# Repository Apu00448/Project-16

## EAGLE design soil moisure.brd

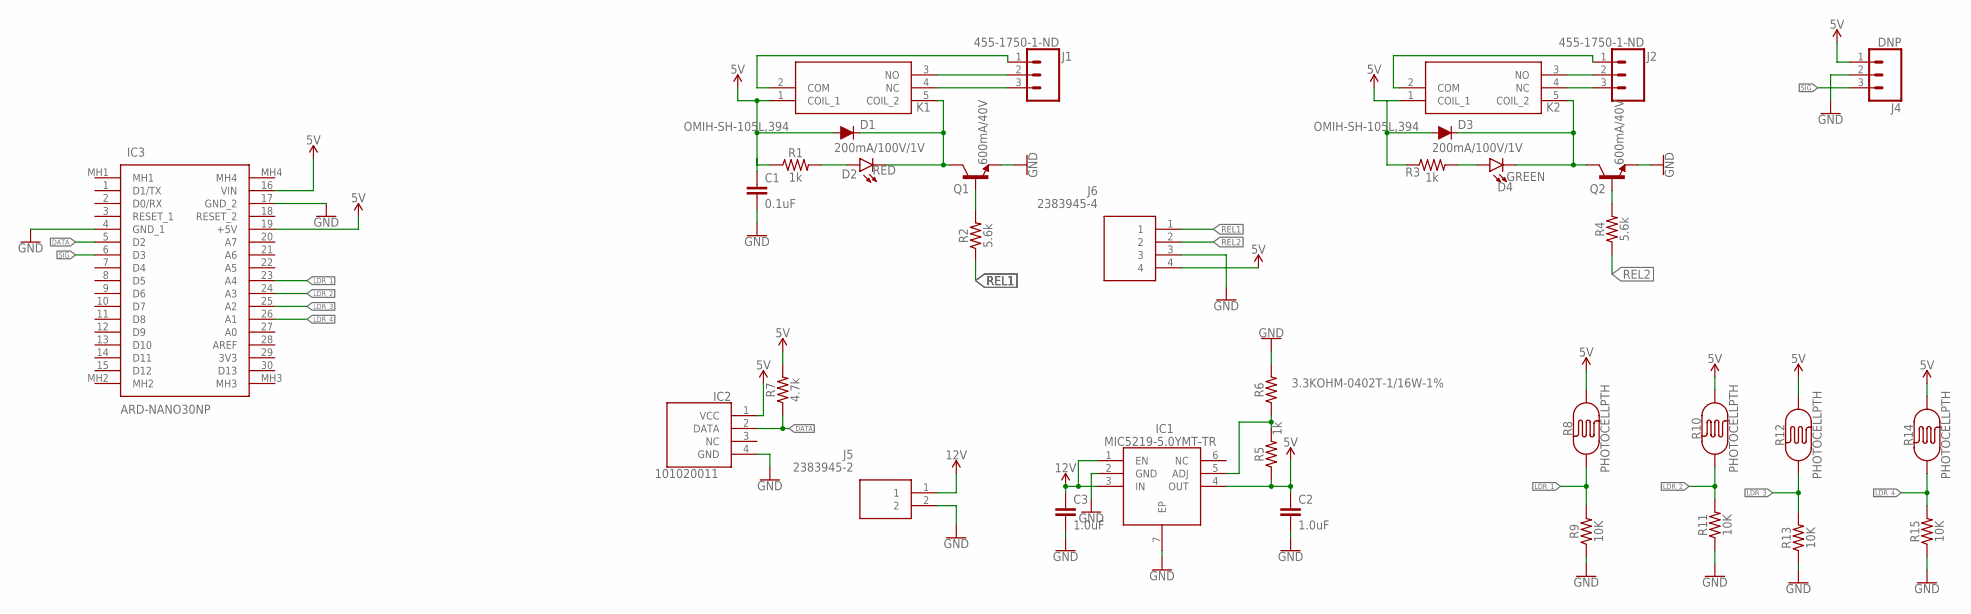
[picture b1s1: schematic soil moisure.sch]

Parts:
C1: 0.1uF; 0402-TIGHT
C2, C3: 1.0uF; 0402-TIGHT
D1, D3: 200mA/100V/1V; DIODE-1N4148
D2: RED; LED-0603
D4: GREEN; LED-0603
IC1: MIC5219-5.0YMT-TR; SON65P200X200X60-7N
IC2: 101020011; HDRV4W80P0X254_1X4_1200X500X15
IC3: ARD-NANO30NP; ARDNANO30NP
J1, J2: 455-1750-1-ND; 1X03
J4: DNP; MOLEX-1X3
J5: 2383945-2; 23839452
J6: 2383945-4; 23839454
K1, K2: OMIH-SH-105L,394; OMIHSH105L394
Q1, Q2: 600mA/40V; SOT23-3
R1, R3, R5: 1k; 0402-TIGHT
R2, R4: 5.6k; 0603
R6: 3.3KOHM-0402T-1/16W-1%; 0402-TIGHT
R7: 4.7k; 0402-TIGHT
R8, R10, R12, R14: PHOTOCELLPTH; PHOTOCELL
R9, R11, R13, R15: 10K; 0402-TIGHT

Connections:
5V: C2.1, D1.A, D3.A, IC1.4 (OUT), IC2.1 (VCC), IC3.16 (VIN), IC3.19 (+5V), J4.1, J6.4, K1.1 (COIL_1), K2.1 (COIL_1), R1.1, R3.1, R5.1, R7.2, R8.2, R10.2, R12.2, R14.2
12V: C3.1, IC1.1 (EN), IC1.3 (IN), J5.1
DATA: IC2.2 (DATA), IC3.5 (D2), R7.1
GND: C1.2, C2.2, C3.2, IC1.2 (GND), IC1.7 (EP), IC2.4 (GND), IC3.4 (GND_1), IC3.17 (GND_2), J4.2, J5.2, J6.3, Q1.2 (E), Q2.2 (E), R6.2, R9.1, R11.1, R13.1, R15.1
LDR_1: IC3.23 (A4), R8.1, R9.2
LDR_2: IC3.24 (A3), R10.1, R11.2
LDR_3: IC3.25 (A2), R12.1, R13.2
LDR_4: IC3.26 (A1), R14.1, R15.2
unnamed: J1.3, K1.4 (NC)
unnamed: J1.2, K1.3 (NO)
unnamed: J1.1, K1.2 (COM)
unnamed: D1.C, D2.C, K1.5 (COIL_2), Q1.3 (C)
unnamed: D2.A, R1.2
unnamed: J2.3, K2.4 (NC)
unnamed: Q1.1 (B), R2.2
unnamed: J2.2, K2.3 (NO)
unnamed: J2.1, K2.2 (COM)
unnamed: D3.C, D4.C, K2.5 (COIL_2), Q2.3 (C)
unnamed: D4.A, R3.2
unnamed: Q2.1 (B), R4.2
unnamed: IC1.5 (ADJ), R5.2, R6.1
REL1: J6.1, R2.1
REL2: J6.2, R4.1
SIG: IC3.6 (D3), J4.3

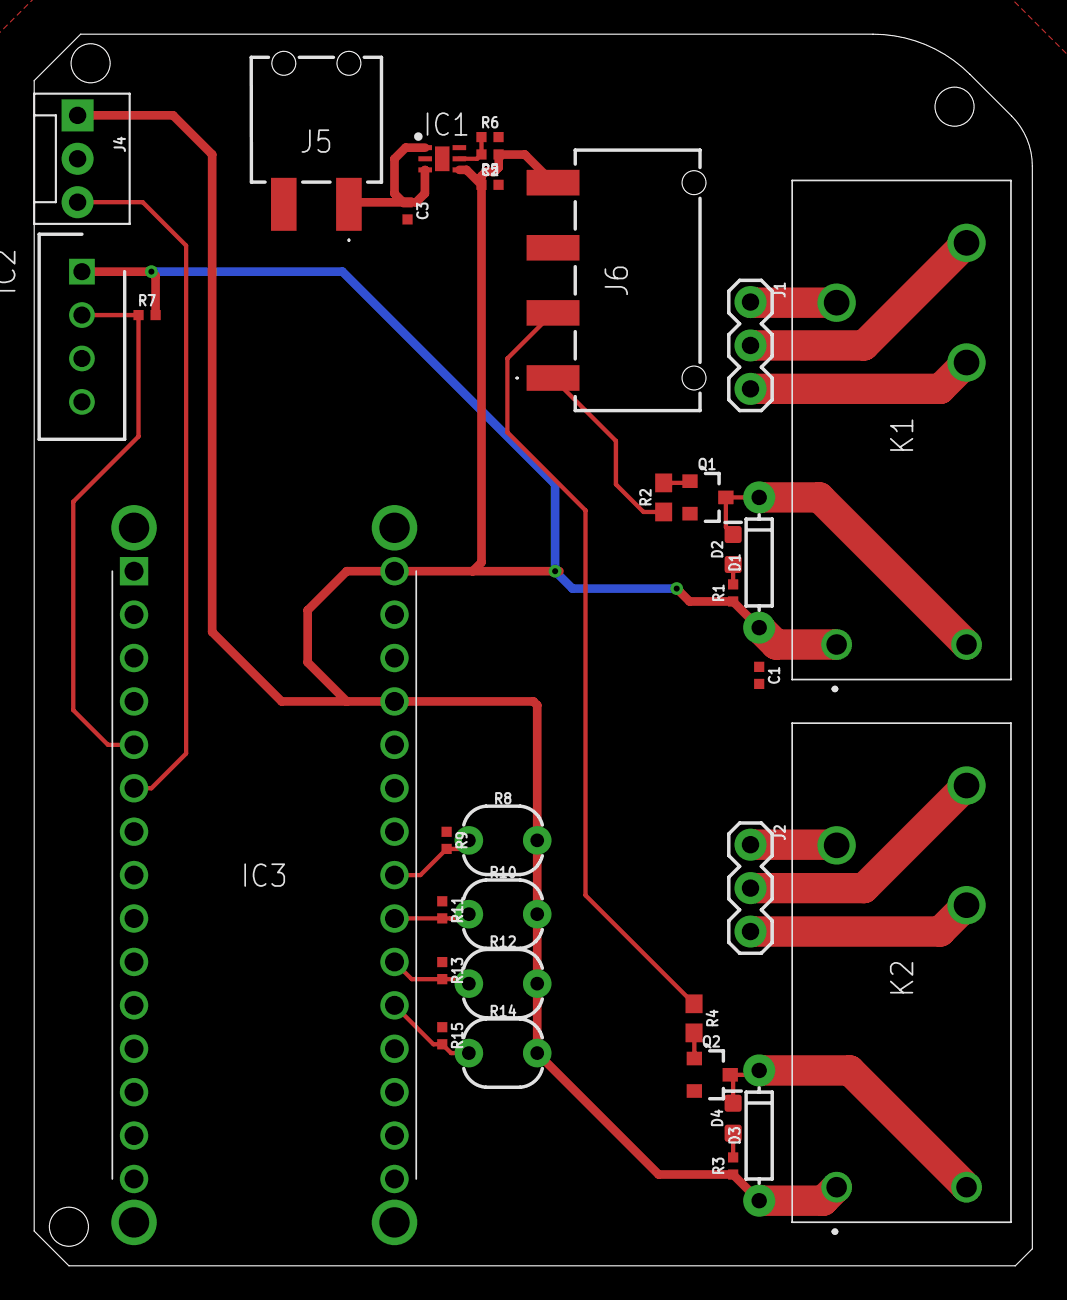
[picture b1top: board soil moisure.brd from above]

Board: 2 copper layers, 58.4 x 72.1 mm, 34 parts (0 on the bottom side), 24 nets.

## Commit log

2024-01-03 Soil Moisture Project- Eagle

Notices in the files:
parts and their libraries:
SparkFun-Capacitors: Licensing: Creative Commons ShareAlike 4.0 International - https://creativecommons.org/licenses/by-sa/4.0
